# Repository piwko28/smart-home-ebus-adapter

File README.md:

# eBUS Adapter for ESP8622

eBUS adapter PCB for use with [ebusd-esp](https://github.com/john30/ebusd-esp) firmware as well as with other UART devices.

Schematic inspired by [ebus adapter 2](https://github.com/eBUS/adapter), so it inherits GPL license.

## Schematic

## PCB design

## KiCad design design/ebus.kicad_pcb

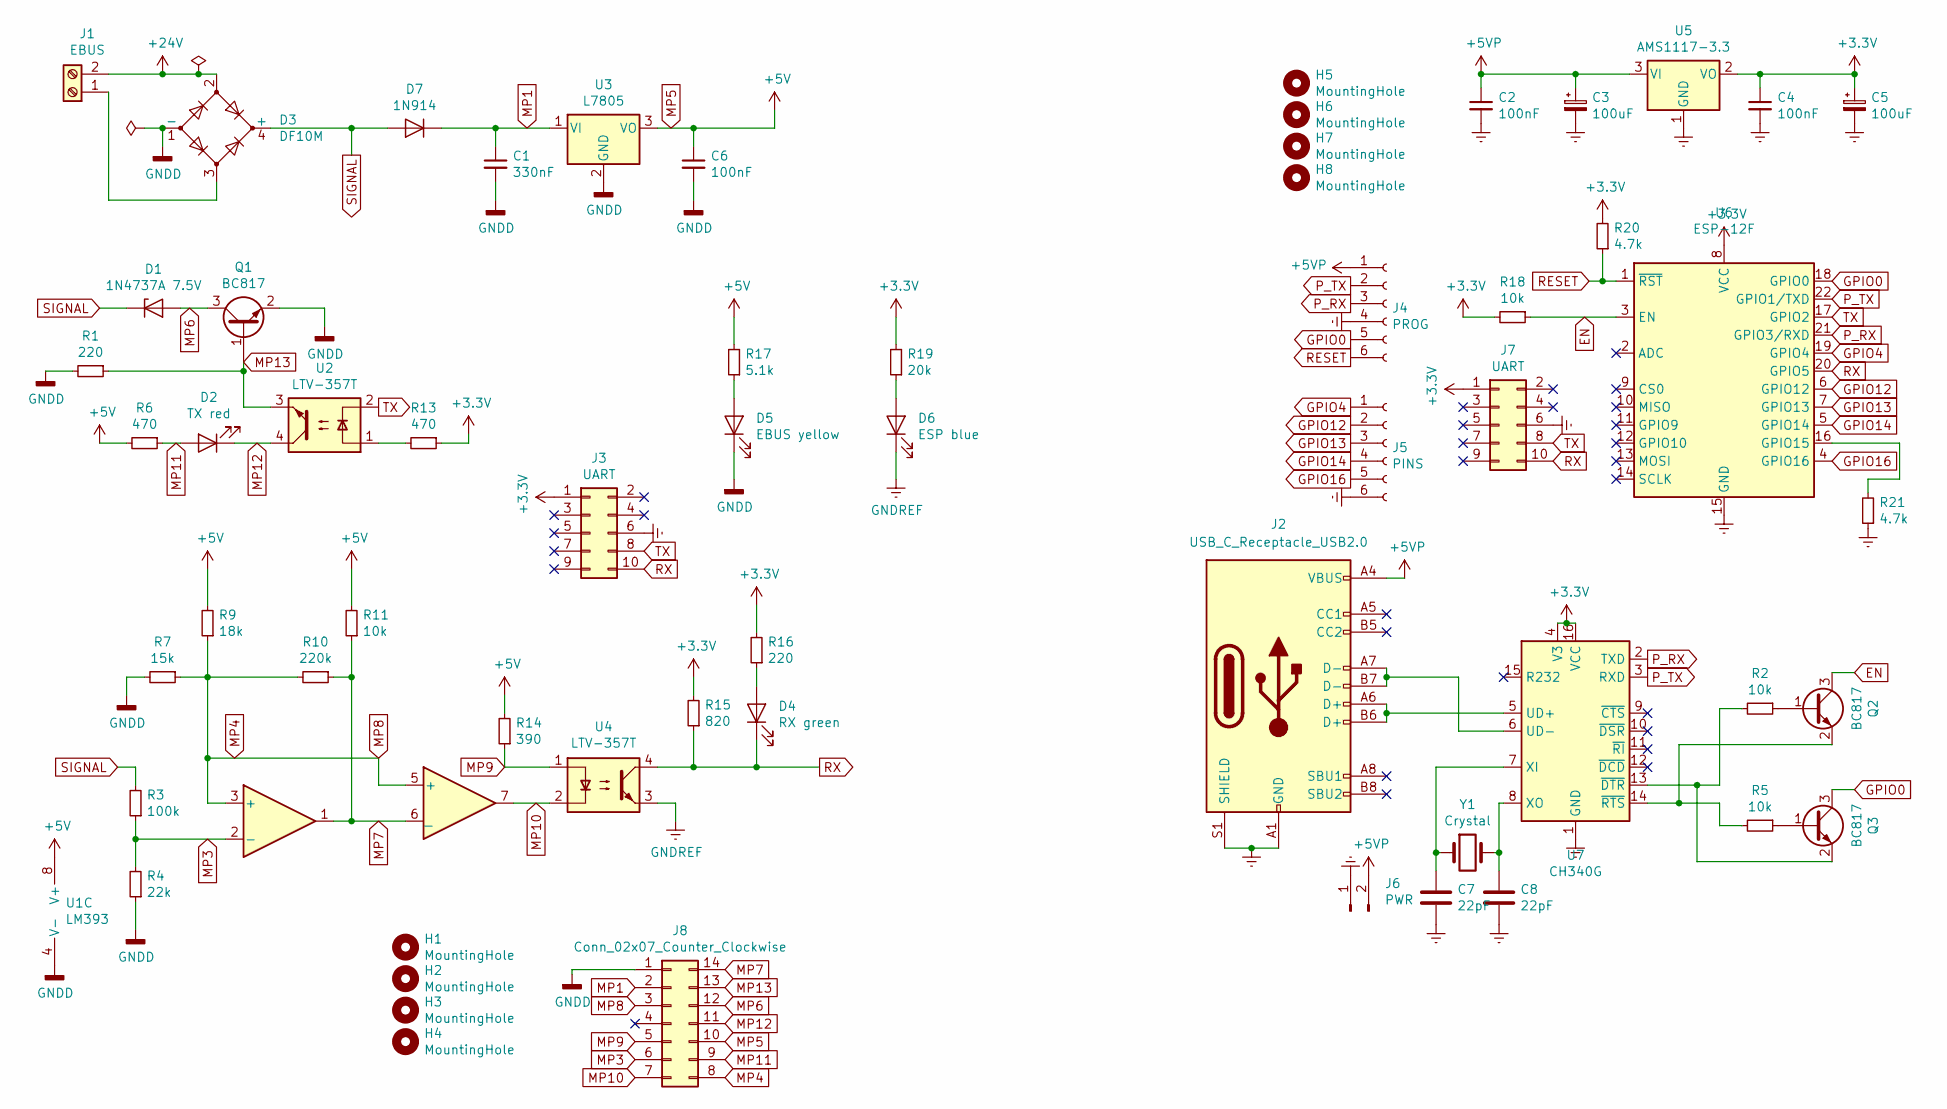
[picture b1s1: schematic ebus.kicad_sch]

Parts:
C1: 330nF; C_1206_3216Metric
C2, C4, C6: 100nF; C_1206_3216Metric
C3, C5: 100uF; CP_Elec_6.3x5.4
C7, C8: 22pF; C_0805_2012Metric
D1: 1N4737A 7.5V; D_SOD-123
D2: TX red; D_1206_3216Metric
D3: DF10M; Diode_Bridge_Bourns_CD-DF4xxS
D4: RX green; D_1206_3216Metric
D5: EBUS yellow; D_1206_3216Metric
D6: ESP blue; D_1206_3216Metric
D7: 1N914; SOT-23
H1, H2, H3, H4, H5, H6, H7, H8: MountingHole; MountingHole_3.2mm_M3
J1: EBUS; TerminalBlock_4Ucon_1x02_P3.50mm_Horizontal
J2: USB_C_Receptacle_USB2.0; USB_C_Receptacle_HRO_TYPE-C-31-M-12
J3: UART; PinSocket_2x05_P2.54mm_Vertical
J4: PROG; PinHeader_1x06_P2.54mm_Vertical
J5: PINS; PinHeader_1x06_P2.54mm_Vertical
J6: PWR; PinHeader_1x02_P2.54mm_Vertical
J7: UART; PinHeader_2x05_P2.54mm_Vertical
J8: Conn_02x07_Counter_Clockwise; PinHeader_2x07_P1.27mm_Vertical
Q1, Q2, Q3: BC817; SOT-23
R1, R16: 220; R_1206_3216Metric
R2, R5, R11, R18: 10k; R_1206_3216Metric
R3: 100k; R_1206_3216Metric
R4: 22k; R_1206_3216Metric
R6, R13: 470; R_1206_3216Metric
R7: 15k; R_1206_3216Metric
R9: 18k; R_1206_3216Metric
R10: 220k; R_1206_3216Metric
R14: 390; R_1206_3216Metric
R15: 820; R_1206_3216Metric
R17: 5.1k; R_1206_3216Metric
R19: 20k; R_1206_3216Metric
R20, R21: 4.7k; R_1206_3216Metric
U1: LM393; SOIC-8_3.9x4.9mm_P1.27mm
U2, U4: LTV-357T; SO-4_4.4x3.6mm_P2.54mm
U3: L7805; TO-263-2
U5: AMS1117-3.3; SOT-223-3_TabPin2
U6: ESP-12F; ESP-12E
U7: CH340G; SOIC-16_3.9x9.9mm_P1.27mm
Y1: Crystal; Crystal_SMD_HC49-SD

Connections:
+3V3: C4.1, C5.1, J3.1, J7.1, R13.1, R15.2, R16.2, R18.2, R19.2, R20.2, U5.2 (VO), U6.8 (VCC), U7.4 (V3), U7.16 (VCC)
+5VP: C2.1, C3.1, J2.A4 (VBUS), J2.A9 (VBUS), J2.B4 (VBUS), J2.B9 (VBUS), J4.1, J6.2, U5.3 (VI)
+24V: D3.2, J1.2
EN: Q2.3 (C), R18.1, U6.3 (EN)
GNDD: C1.2, C6.2, D3.1 (-), D5.1 (K), J8.1, Q1.2 (E), R1.2, R4.1, R7.2, U1.4 (V-), U3.2 (GND)
GNDREF: C2.2, C3.2, C4.2, C5.2, C7.2, C8.2, D6.1 (K), J2.A1 (GND), J2.A12 (GND), J2.B1 (GND), J2.B12 (GND), J2.S1 (SHIELD), J3.6, J4.4, J5.6, J6.1, J7.6, R21.1, U4.3, U5.1 (GND), U6.15 (GND), U7.1 (GND)
GPIO0: J4.5, Q3.3 (C), U6.18 (GPIO0)
GPIO4: J5.1, U6.19 (GPIO4)
GPIO12: J5.2, U6.6 (GPIO12)
GPIO13: J5.3, U6.7 (GPIO13)
GPIO14: J5.4, U6.5 (GPIO14)
GPIO16: J5.5, U6.4 (GPIO16)
MP1: C1.1, D7.3 (K), J8.2, U3.1 (VI)
MP3: J8.6, R3.1, R4.2, U1.2 (-)
MP4: J8.3, J8.8, R7.1, R9.1, R10.2, U1.3 (+), U1.5 (+)
MP5: C6.1, J8.10, R6.2, R9.2, R11.2, R14.2, R17.2, U1.8 (V+), U3.3 (VO)
MP6: D1.2 (A), J8.12, Q1.3 (C)
MP7: J8.14, R10.1, R11.1, U1.1, U1.6 (_)
MP9: J8.5, R14.1, U4.1
MP10: J8.7, U1.7, U4.2
MP11: D2.2 (A), J8.9, R6.1
MP12: D2.1 (K), J8.11, U2.4
MP13: J8.13, Q1.1 (B), R1.1, U2.3
unnamed: C7.1, U7.7 (XI), Y1.1
unnamed: C8.1, U7.8 (XO), Y1.2
unnamed: D3.3, J1.1
unnamed: D4.2 (A), R16.1
unnamed: D5.2 (A), R17.1
unnamed: D6.2 (A), R19.1
unnamed: Q2.1 (B), R2.1
unnamed: Q2.2 (E), R5.2, U7.14 (~RTS)
unnamed: Q3.1 (B), R5.1
unnamed: Q3.2 (E), R2.2, U7.13 (~DTR)
unnamed: R13.2, U2.1
unnamed: R21.2, U6.16 (GPIO15)
unnamed: J2.A6 (D+), J2.B6 (D+), U7.5 (UD+)
unnamed: J2.A7 (D-), J2.B7 (D-), U7.6 (UD-)
P_RX: J4.3, U6.21 (GPIO3/RXD), U7.2 (TXD)
P_TX: J4.2, U6.22 (GPIO1/TXD), U7.3 (RXD)
RESET: J4.6, R20.1, U6.1 (~RST)
RX: D4.1 (K), J3.10, J7.10, R15.1, U4.4, U6.20 (GPIO5)
SIGNAL: D1.1 (K), D3.4 (+), D7.1 (A), R3.2
TX: J3.8, J7.8, U2.2, U6.17 (GPIO2)

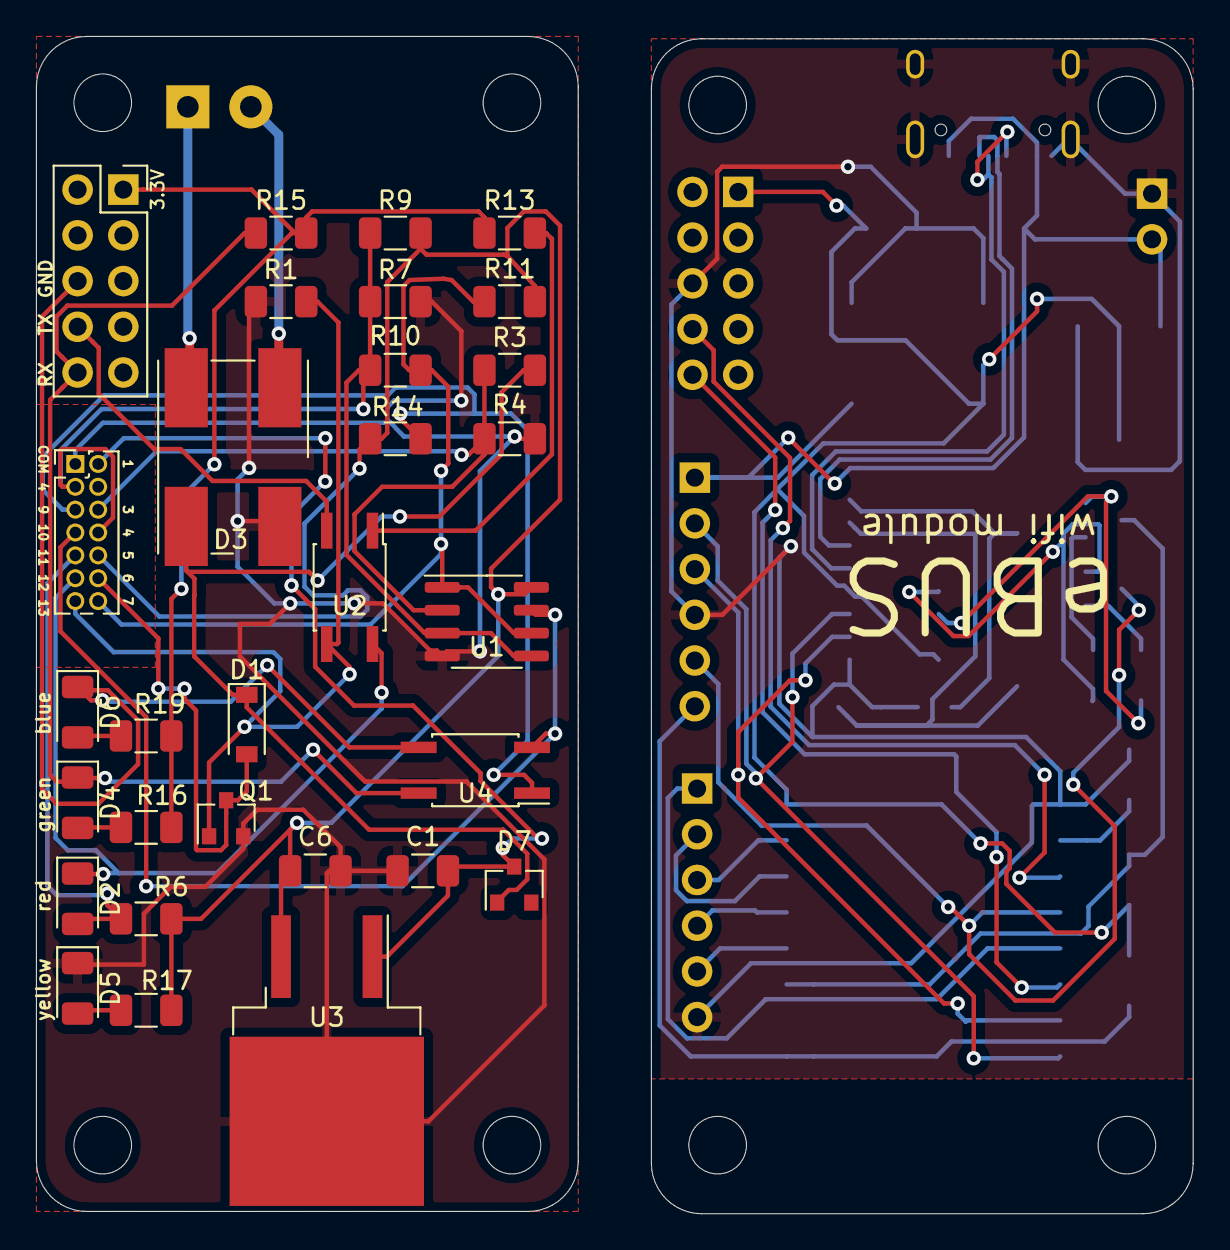
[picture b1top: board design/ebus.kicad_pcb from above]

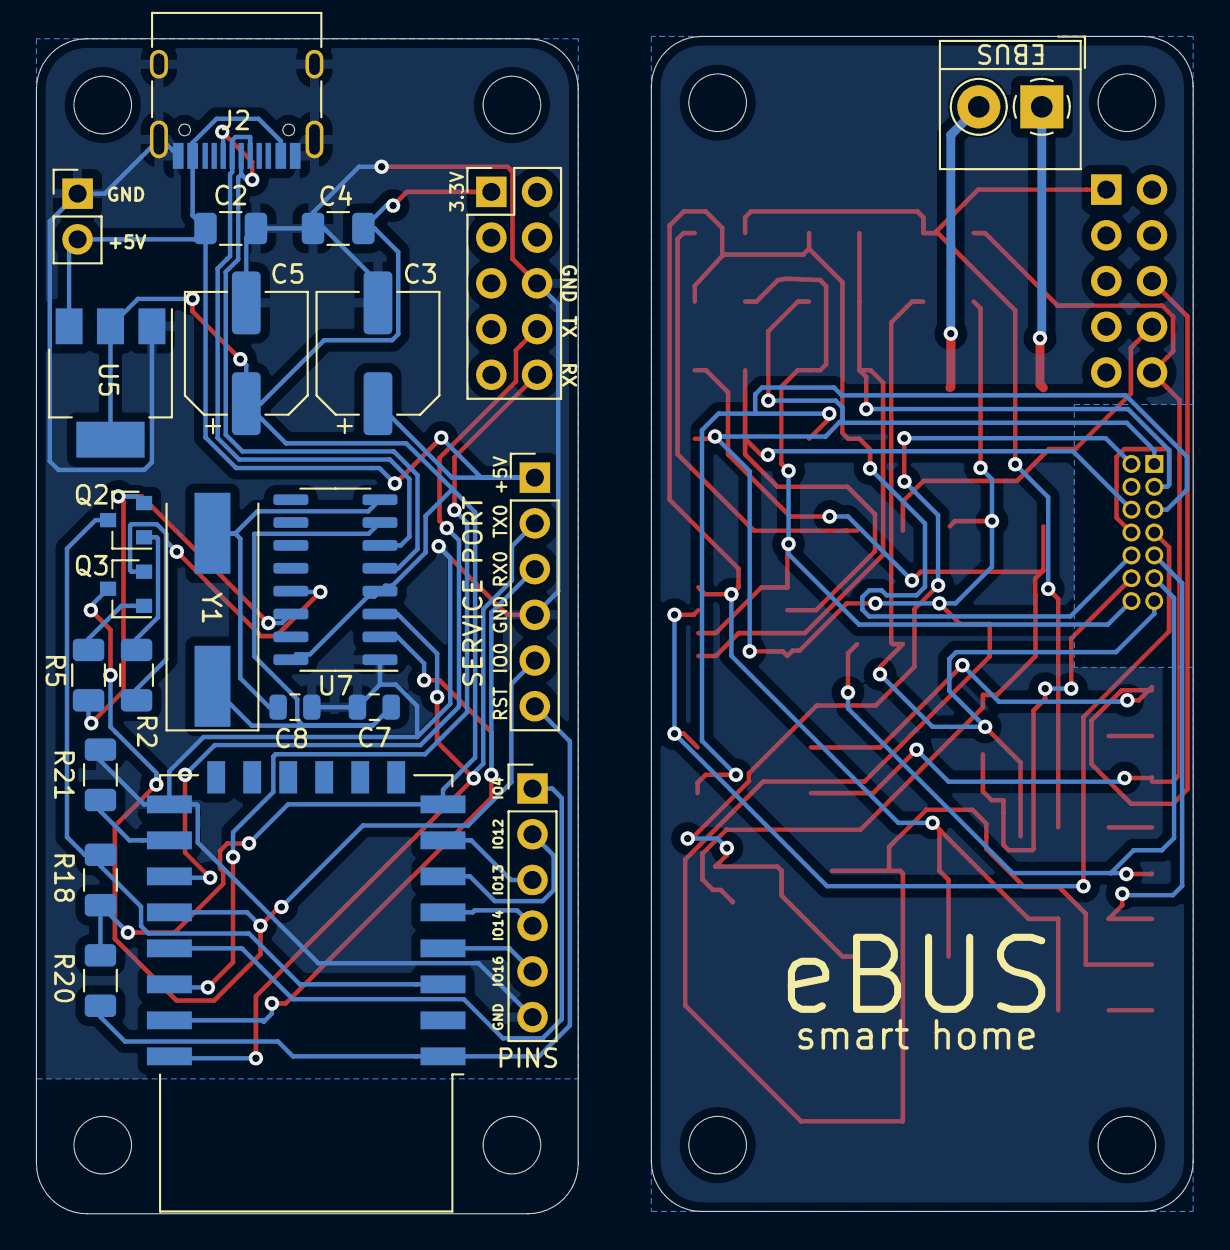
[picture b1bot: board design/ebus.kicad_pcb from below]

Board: 2 copper layers, 64.3 x 65.4 mm, 61 parts (27 on the bottom side), 43 nets.

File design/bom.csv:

"Source:","/home/szymon/Projects/smart-home/ebus/ebus/design/ebus.sch"
"Date:","Wed 03 Nov 2021 11:00:56 CET"
"Tool:","Eeschema 5.1.5+dfsg1-2build2"
"Component Count:","47"
"Ref","Value","Footprint","Datasheet","Manufacturer","Vendor"
"C1","330nF","Capacitor_THT:C_Disc_D5.0mm_W2.5mm_P2.50mm","~","",""
"C2","100nF","Capacitor_SMD:C_1206_3216Metric","~","",""
"C3","100uF","Capacitor_SMD:CP_Elec_5x5.7","~","",""
"C4","100nF","Capacitor_SMD:C_1206_3216Metric","~","",""
"C5","100uF","Capacitor_SMD:CP_Elec_5x5.7","~","",""
"C6","100nF","Capacitor_THT:C_Disc_D5.0mm_W2.5mm_P2.50mm","~","",""
"D1","1N4737A 9.1V","Diode_THT:D_DO-41_SOD81_P10.16mm_Horizontal","http://www.vishay.com/docs/85790/zpy3v9.pdf","",""
"D2","TX red","LED_THT:LED_D3.0mm_Horizontal_O1.27mm_Z2.0mm","~","",""
"D3","DF10M","Diode_THT:Diode_Bridge_DIP-4_W7.62mm_P5.08mm","http://www.vishay.com/docs/88571/dfm.pdf","",""
"D4","RX green","LED_THT:LED_D3.0mm_Horizontal_O1.27mm_Z2.0mm","~","",""
"D5","EBUS yellow","LED_THT:LED_D3.0mm_Horizontal_O1.27mm_Z2.0mm","~","",""
"D6","ESP blue","LED_THT:LED_D3.0mm_Horizontal_O1.27mm_Z2.0mm","~","",""
"D7","1N914","Diode_THT:D_DO-35_SOD27_P7.62mm_Horizontal","http://www.vishay.com/docs/85622/1n914.pdf","",""
"J1","EBUS","TerminalBlock_4Ucon:TerminalBlock_4Ucon_1x02_P3.50mm_Horizontal","~","",""
"J2","UART","Connector_PinHeader_2.54mm:PinHeader_1x04_P2.54mm_Vertical","~","",""
"J3","USB_B_Micro","Connector_USB:USB_Micro-B_Wuerth_629105150521","~","",""
"J4","PWR","Connector_PinHeader_2.54mm:PinHeader_1x02_P2.54mm_Vertical","~","",""
"J5","SERVICE","Connector_PinHeader_2.54mm:PinHeader_1x02_P2.54mm_Vertical","~","",""
"J6","PROG","Connector_PinHeader_2.54mm:PinHeader_1x04_P2.54mm_Vertical","~","",""
"J7","TX test","Connector_PinHeader_2.54mm:PinHeader_1x02_P2.54mm_Vertical","~","",""
"J8","TX switch","Connector_PinHeader_2.54mm:PinHeader_1x02_P2.54mm_Vertical","~","",""
"J9","RX switch","Connector_PinHeader_2.54mm:PinHeader_1x02_P2.54mm_Vertical","~","",""
"J10","Measurements","Connector_PinHeader_2.54mm:PinHeader_2x07_P2.54mm_Vertical","~","",""
"Q1","BC337-40","Package_TO_SOT_THT:TO-92_Inline","https://diotec.com/tl_files/diotec/files/pdf/datasheets/bc337.pdf","",""
"R1","220","Resistor_THT:R_Axial_DIN0207_L6.3mm_D2.5mm_P7.62mm_Horizontal","~","",""
"R3","100k","Resistor_THT:R_Axial_DIN0207_L6.3mm_D2.5mm_P7.62mm_Horizontal","~","",""
"R4","22k","Resistor_THT:R_Axial_DIN0207_L6.3mm_D2.5mm_P7.62mm_Horizontal","~","",""
"R6","470","Resistor_THT:R_Axial_DIN0207_L6.3mm_D2.5mm_P7.62mm_Horizontal","~","",""
"R7","15k","Resistor_THT:R_Axial_DIN0207_L6.3mm_D2.5mm_P7.62mm_Horizontal","~","",""
"R9","18k","Resistor_THT:R_Axial_DIN0207_L6.3mm_D2.5mm_P7.62mm_Horizontal","~","",""
"R10","220k","Resistor_THT:R_Axial_DIN0207_L6.3mm_D2.5mm_P7.62mm_Horizontal","~","",""
"R11","10k","Resistor_THT:R_Axial_DIN0207_L6.3mm_D2.5mm_P7.62mm_Horizontal","~","",""
"R13","470","Resistor_THT:R_Axial_DIN0207_L6.3mm_D2.5mm_P7.62mm_Horizontal","~","",""
"R14","390","Resistor_THT:R_Axial_DIN0207_L6.3mm_D2.5mm_P7.62mm_Horizontal","~","",""
"R15","820","Resistor_THT:R_Axial_DIN0207_L6.3mm_D2.5mm_P7.62mm_Horizontal","~","",""
"R16","220","Resistor_THT:R_Axial_DIN0207_L6.3mm_D2.5mm_P7.62mm_Horizontal","~","",""
"R17","10k","Resistor_THT:R_Axial_DIN0207_L6.3mm_D2.5mm_P7.62mm_Horizontal","~","",""
"R18","10k","Resistor_SMD:R_1206_3216Metric","~","",""
"R19","10k","Resistor_THT:R_Axial_DIN0207_L6.3mm_D2.5mm_P7.62mm_Horizontal","~","",""
"R20","4.7k","Resistor_SMD:R_1206_3216Metric","~","",""
"R21","4.7k","Resistor_SMD:R_1206_3216Metric","~","",""
"U1","AMP","Package_DIP:DIP-8_W7.62mm","http://www.ti.com/lit/ds/symlink/lm393.pdf","",""
"U2","OTX","Package_DIP:DIP-6_W7.62mm","http://www.ti.com/lit/ds/symlink/lm393.pdf","",""
"U3","L7805","Package_TO_SOT_THT:TO-220-3_Horizontal_TabDown","http://www.ti.com/lit/ds/symlink/lm393.pdf","",""
"U4","ORX","Package_DIP:DIP-6_W7.62mm","http://www.ti.com/lit/ds/symlink/lm393.pdf","",""
"U5","ESP-12F","RF_Module:ESP-12E","http://wiki.ai-thinker.com/_media/esp8266/esp8266_series_mod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","",""
"U6","AMS1117-3.3","Package_TO_SOT_SMD:SOT-223-3_TabPin2","http://www.advanced-monolithic.com/pdf/ds1117.pdf","",""

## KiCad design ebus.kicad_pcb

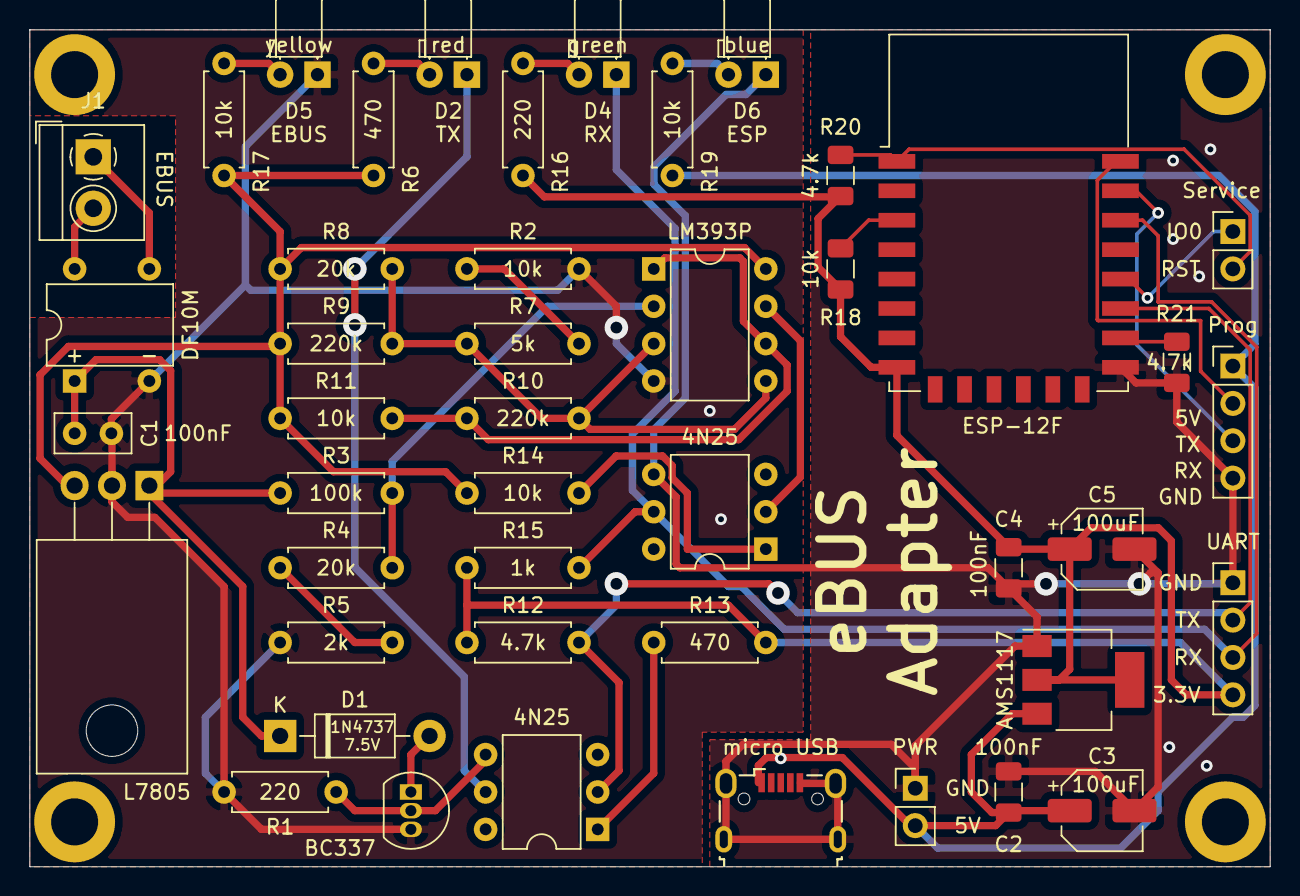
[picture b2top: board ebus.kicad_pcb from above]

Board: 2 copper layers, 84.3 x 56.9 mm, 45 parts (0 on the bottom side), 31 nets.

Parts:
4N25, 4N25#2: 4N25; DIP-6_W7.62mm
AMS1117: AMS1117-3.3; SOT-223-3_TabPin2
BC337: BC337; TO-92_Inline
C1: 100nF; C_Disc_D5.0mm_W2.5mm_P2.50mm
C2, C4: 100nF; C_1206_3216Metric
C3, C5: 100uF; CP_Elec_5x5.7
D1: 1N4737A 7.5V; D_DO-41_SOD81_P10.16mm_Horizontal
D2: TX red; LED_D3.0mm_Horizontal_O1.27mm_Z2.0mm
D4: RX green; LED_D3.0mm_Horizontal_O1.27mm_Z2.0mm
D5: EBUS yellow; LED_D3.0mm_Horizontal_O1.27mm_Z2.0mm
D6: ESP blue; LED_D3.0mm_Horizontal_O1.27mm_Z2.0mm
DF10M: DF10M; Diode_Bridge_DIP-4_W7.62mm_P5.08mm
ESP-12F: ESP-12F; ESP-12E
J1: EBUS; TerminalBlock_4Ucon_1x02_P3.50mm_Horizontal
L7805: L7805; TO-220-3_Horizontal_TabDown
LM393P: LM393; DIP-8_W7.62mm
PWR: PWR; PinHeader_1x02_P2.54mm_Vertical
Prog: PROG; PinHeader_1x04_P2.54mm_Vertical
R1, R16: 220; R_Axial_DIN0207_L6.3mm_D2.5mm_P7.62mm_Horizontal
R2, R11, R14, R17, R19: 10k; R_Axial_DIN0207_L6.3mm_D2.5mm_P7.62mm_Horizontal
R3: 100k; R_Axial_DIN0207_L6.3mm_D2.5mm_P7.62mm_Horizontal
R4, R8: 20k; R_Axial_DIN0207_L6.3mm_D2.5mm_P7.62mm_Horizontal
R5: 2k; R_Axial_DIN0207_L6.3mm_D2.5mm_P7.62mm_Horizontal
R6, R13: 470; R_Axial_DIN0207_L6.3mm_D2.5mm_P7.62mm_Horizontal
R7: 5.1k; R_Axial_DIN0207_L6.3mm_D2.5mm_P7.62mm_Horizontal
R9, R10: 220k; R_Axial_DIN0207_L6.3mm_D2.5mm_P7.62mm_Horizontal
R12: 4.7k; R_Axial_DIN0207_L6.3mm_D2.5mm_P7.62mm_Horizontal
R15: 1k; R_Axial_DIN0207_L6.3mm_D2.5mm_P7.62mm_Horizontal
R18: 10k; R_1206_3216Metric
R20, R21: 4.7k; R_1206_3216Metric
Service: SERVICE; PinHeader_1x02_P2.54mm_Vertical
UART: UART; PinHeader_1x04_P2.54mm_Vertical
micro USB: USB_B_Micro; USB_Micro-B_Wuerth_629105150521

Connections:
+3V3: AMS1117.2, C4.1, C5.1, ESP-12F.8, R12.2, R13.1, R15.2, R16.2, R18.1, R20.2, UART.4
+5V: L7805.3, LM393P.8, R6.2, R8.2, R9.2, R11.2, R14.2, R17.2
+5VP: AMS1117.3, C2.1, C3.1, PWR.2, Prog.1, R19.2, micro USB.1
GNDD: BC337.3, C1.2, D5.1, DF10M.2, L7805.2, LM393P.4, R1.2, R2.2, R5.1
GNDREF: 4N25.4, AMS1117.1, C2.2, C3.2, C4.2, C5.2, D6.1, ESP-12F.15, PWR.1, Prog.4, R21.2, UART.1, micro USB.5, micro USB.6
GPIO0: ESP-12F.18, Service.1
unnamed: BC337.1, D1.2
unnamed: 4N25#2.5, D2.1
unnamed: D2.2, R6.1
unnamed: DF10M.3, J1.1
unnamed: DF10M.4, J1.2
unnamed: D4.2, R16.1
unnamed: D5.2, R17.1
unnamed: D6.2, R19.1
unnamed: 4N25#2.4, BC337.2, R1.1
unnamed: R2.1, R7.2
unnamed: LM393P.2, R3.1, R4.2
unnamed: R4.1, R5.2
unnamed: LM393P.1, LM393P.6, R10.1, R11.1
unnamed: LM393P.3, LM393P.5, R7.1, R8.1, R9.1, R10.2
unnamed: 4N25#2.1, R13.2
unnamed: 4N25.1, R14.1
unnamed: ESP-12F.3, R18.2
unnamed: ESP-12F.16, R21.1
unnamed: 4N25.2, LM393P.7
P_RX: ESP-12F.21, Prog.3
P_TX: ESP-12F.22, Prog.2
RESET: ESP-12F.1, R20.1, Service.2
RX: 4N25.5, D4.1, ESP-12F.20, R15.1, UART.3
SIGNAL: C1.1, D1.1, DF10M.1, L7805.1, R3.2
TX: 4N25#2.2, ESP-12F.17, R12.1, UART.2

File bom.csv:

Label,Quantity,Part name,Package
4N25,2,4N25,DIP-6_W7.62mm
"C4,C2",2,100nF,C_1206_3216Metric
"R21,R20",2,4.7k,R_1206_3216Metric
R18,1,10k,R_1206_3216Metric
AMS1117,1,AMS1117-3.3,SOT-223-3_TabPin2
ESP-12F,1,ESP-12F,ESP-12E
L7805,1,L7805,TO-220-3_Horizontal_TabDown
LM393P,1,LM393,DIP-8_W7.62mm
"R19,R17,R14,R11,R2",5,10k,R_Axial_DIN0207_L6.3mm_D2.5mm_P7.62mm_Horizontal
"R16,R1",2,220,R_Axial_DIN0207_L6.3mm_D2.5mm_P7.62mm_Horizontal
R15,1,1k,R_Axial_DIN0207_L6.3mm_D2.5mm_P7.62mm_Horizontal
"R13,R6",2,470,R_Axial_DIN0207_L6.3mm_D2.5mm_P7.62mm_Horizontal
R12,1,4.7k,R_Axial_DIN0207_L6.3mm_D2.5mm_P7.62mm_Horizontal
"R10,R9",2,220k,R_Axial_DIN0207_L6.3mm_D2.5mm_P7.62mm_Horizontal
"R8,R4",2,20k,R_Axial_DIN0207_L6.3mm_D2.5mm_P7.62mm_Horizontal
R7,1,5.1k,R_Axial_DIN0207_L6.3mm_D2.5mm_P7.62mm_Horizontal
R5,1,2k,R_Axial_DIN0207_L6.3mm_D2.5mm_P7.62mm_Horizontal
R3,1,100k,R_Axial_DIN0207_L6.3mm_D2.5mm_P7.62mm_Horizontal
BC337,1,BC337,TO-92_Inline
Prog,1,PROG,PinHeader_1x04_P2.54mm_Vertical
Service,1,SERVICE,PinHeader_1x02_P2.54mm_Vertical
PWR,1,PWR,PinHeader_1x02_P2.54mm_Vertical
micro USB,1,USB_B_Micro,USB_Micro-B_Wuerth_629105150521
UART,1,UART,PinHeader_1x04_P2.54mm_Vertical
J1,1,EBUS,TerminalBlock_4Ucon_1x02_P3.50mm_Horizontal
D6,1,ESP blue,LED_D3.0mm_Horizontal_O1.27mm_Z2.0mm
D5,1,EBUS yellow,LED_D3.0mm_Horizontal_O1.27mm_Z2.0mm
D4,1,RX green,LED_D3.0mm_Horizontal_O1.27mm_Z2.0mm
DF10M,1,DF10M,Diode_Bridge_DIP-4_W7.62mm_P5.08mm
D2,1,TX red,LED_D3.0mm_Horizontal_O1.27mm_Z2.0mm
D1,1,1N4737A 7.5V,D_DO-41_SOD81_P10.16mm_Horizontal
"C5,C3",2,100uF,CP_Elec_5x5.7
C1,1,100nF,C_Disc_D5.0mm_W2.5mm_P2.50mm

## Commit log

2021-01-27 Ebus adapter init
2021-01-27 PCB redesigned and with labels
2021-01-27 Gerber files
2021-01-27 Readme
2021-01-27 Box design
2021-01-28 Create LICENSE
2021-01-28 Mistake in R14 resistor value fix
2021-01-28 Clean up repository
2021-01-28 Voltage regulator changes, some graphical improvements of pcb
2021-02-02 SMD PCB for Raspberry PI Zero
2021-02-02 Fix for pins in wrong place
2021-02-25 Wrong transistor case
2021-09-24 Raspberry something
2021-10-29 PCB v1.1 - added measurements points, reduced number of resistors, changed components values
2021-10-29 Home assistant configurations and scripts
2021-11-03 Change usb socket footprint
2021-11-04 Raspberry board update
2021-11-04 Gerbers
2021-11-11 HA configuration for 720
2021-11-27 Fix missing track
2021-11-27 Dashboard example
2022-01-10 Remove stdbuf from read-properties - unneeded and there is no stdbuf in docker
2022-02-21 Added vrc700 to simplify integration
2022-03-24 Inverted rx-tx, reposition ebus terminal with measurement points to let attach raspberry with full connector, added programmer to wifi module
2023-10-06 usbc, updated images
2023-10-06 Updated images
2024-10-07 HA configurations for new requirements
